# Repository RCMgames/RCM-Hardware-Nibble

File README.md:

# RCM-Hardware-Nibble
v1.8

Half a [BYTE](https://github.com/RCMgames/RCM-Hardware-BYTE)

* 1.08 by 1.12 inches, 27.432 by 28.448 millimeters
* 4 motors
* 4 servos
* 2 additional GPIO pins
* built-in [IMU](https://github.com/RCMgames/useful-code/blob/main/sensors/IMUs/ICM20948/ICM20948_helper.h)
* battery monitoring
* I2C connector on QT PY
* runs on 3-11 volts

program with [RCMv2](https://github.com/RCMgames/RCMv2)

### Tested with the following types of ESP32 QT Py:
| Type of QT Py | PlatformIO name | link to Adafruit |
| ------ | -------- | -------- |
| S3 with 2MB PSRAM |  adafruit_qtpy_esp32s3_n4r2   |  https://www.adafruit.com/product/5700   |
| S3 with 8Mb Flash |  adafruit_qtpy_esp32s3_nopsram   |  https://www.adafruit.com/product/5426   |
| S2 |  adafruit_qtpy_esp32s2   |  https://www.adafruit.com/product/5325  |

Look here for how to program it: https://github.com/RCMgames/RCMv2

Look here for more information and examples of robots: https://github.com/rcmgames

Want slightly larger and 8 motors and 8 servos? Look at the [BYTE](https://github.com/rcmgames/RCM-Hardware-BYTE)

## Options for purchasing

* [PCBWay link](https://www.pcbway.com/project/shareproject/RCMhardwareNibble_v1_8_dbf51cb4.html) (PCBWay will give me a commission without increasing the price for you). (approximately $110 for 2 boards and manufacturing took a month).
* send the gerbers, bill of materials, and ComponentPlacement files (in /PCBproduction-RCM-Nibble) to a PCB manufacturer of your choice (details you may be asked for: min hole 0.25mm, min track/spacing 5/5mil, thickness 1.0mm, 1 oz Cu outer 1.5 oz Cu inner, tell them to not solder the icm20948's exposed pad)

## Components
Solder by hand to complete the assembly of your boards.
| part | links | quantity | notes |
| ----- | ----- | ----- | ----- |
| RCM Nibble circuit board | [options for purchasing](https://github.com/RCMgames/RCM-Hardware-Nibble/tree/main#options-for-purchasing) | 1 | |
| ESP32 QT Py | [compatible QT Py](https://github.com/RCMgames/RCM-Hardware-Nibble/tree/main#tested-with-the-following-types-of-esp32-qt-py) | 1 | |
| 2x4 female header pins | [this](https://www.digikey.com/en/products/detail/sullins-connector-solutions/PPPC042LFBN-RC/810244) or 2 strips of 4 | 1 | for motors |
| 7 female header pins | | 2 | for QT Py |
| 3 male header pins | | 4 | for servos |
| 2 male header pins | | 2 | for extra GPIO pins |
| battery wires | JST RCY OR 9V battery snap | 1 | [Amazon JST RCY](https://www.amazon.com/dp/B00Z04QFN2/) |
| servo buck boost 5v 2A | [Pololu](https://www.pololu.com/product/4085) | 0 or 1 | if you want to supply voltages above or below what servos can accept (supplies other than 5AAs) |

## Acknowledgements
* I would like to thank [PCBWay](https://www.pcbway.com/) for sponsoring prototyping runs of this project. PCBWay produces very nice boards, supports open source hardware, and gave me great support as I worked on this project. Special thanks to Liam!

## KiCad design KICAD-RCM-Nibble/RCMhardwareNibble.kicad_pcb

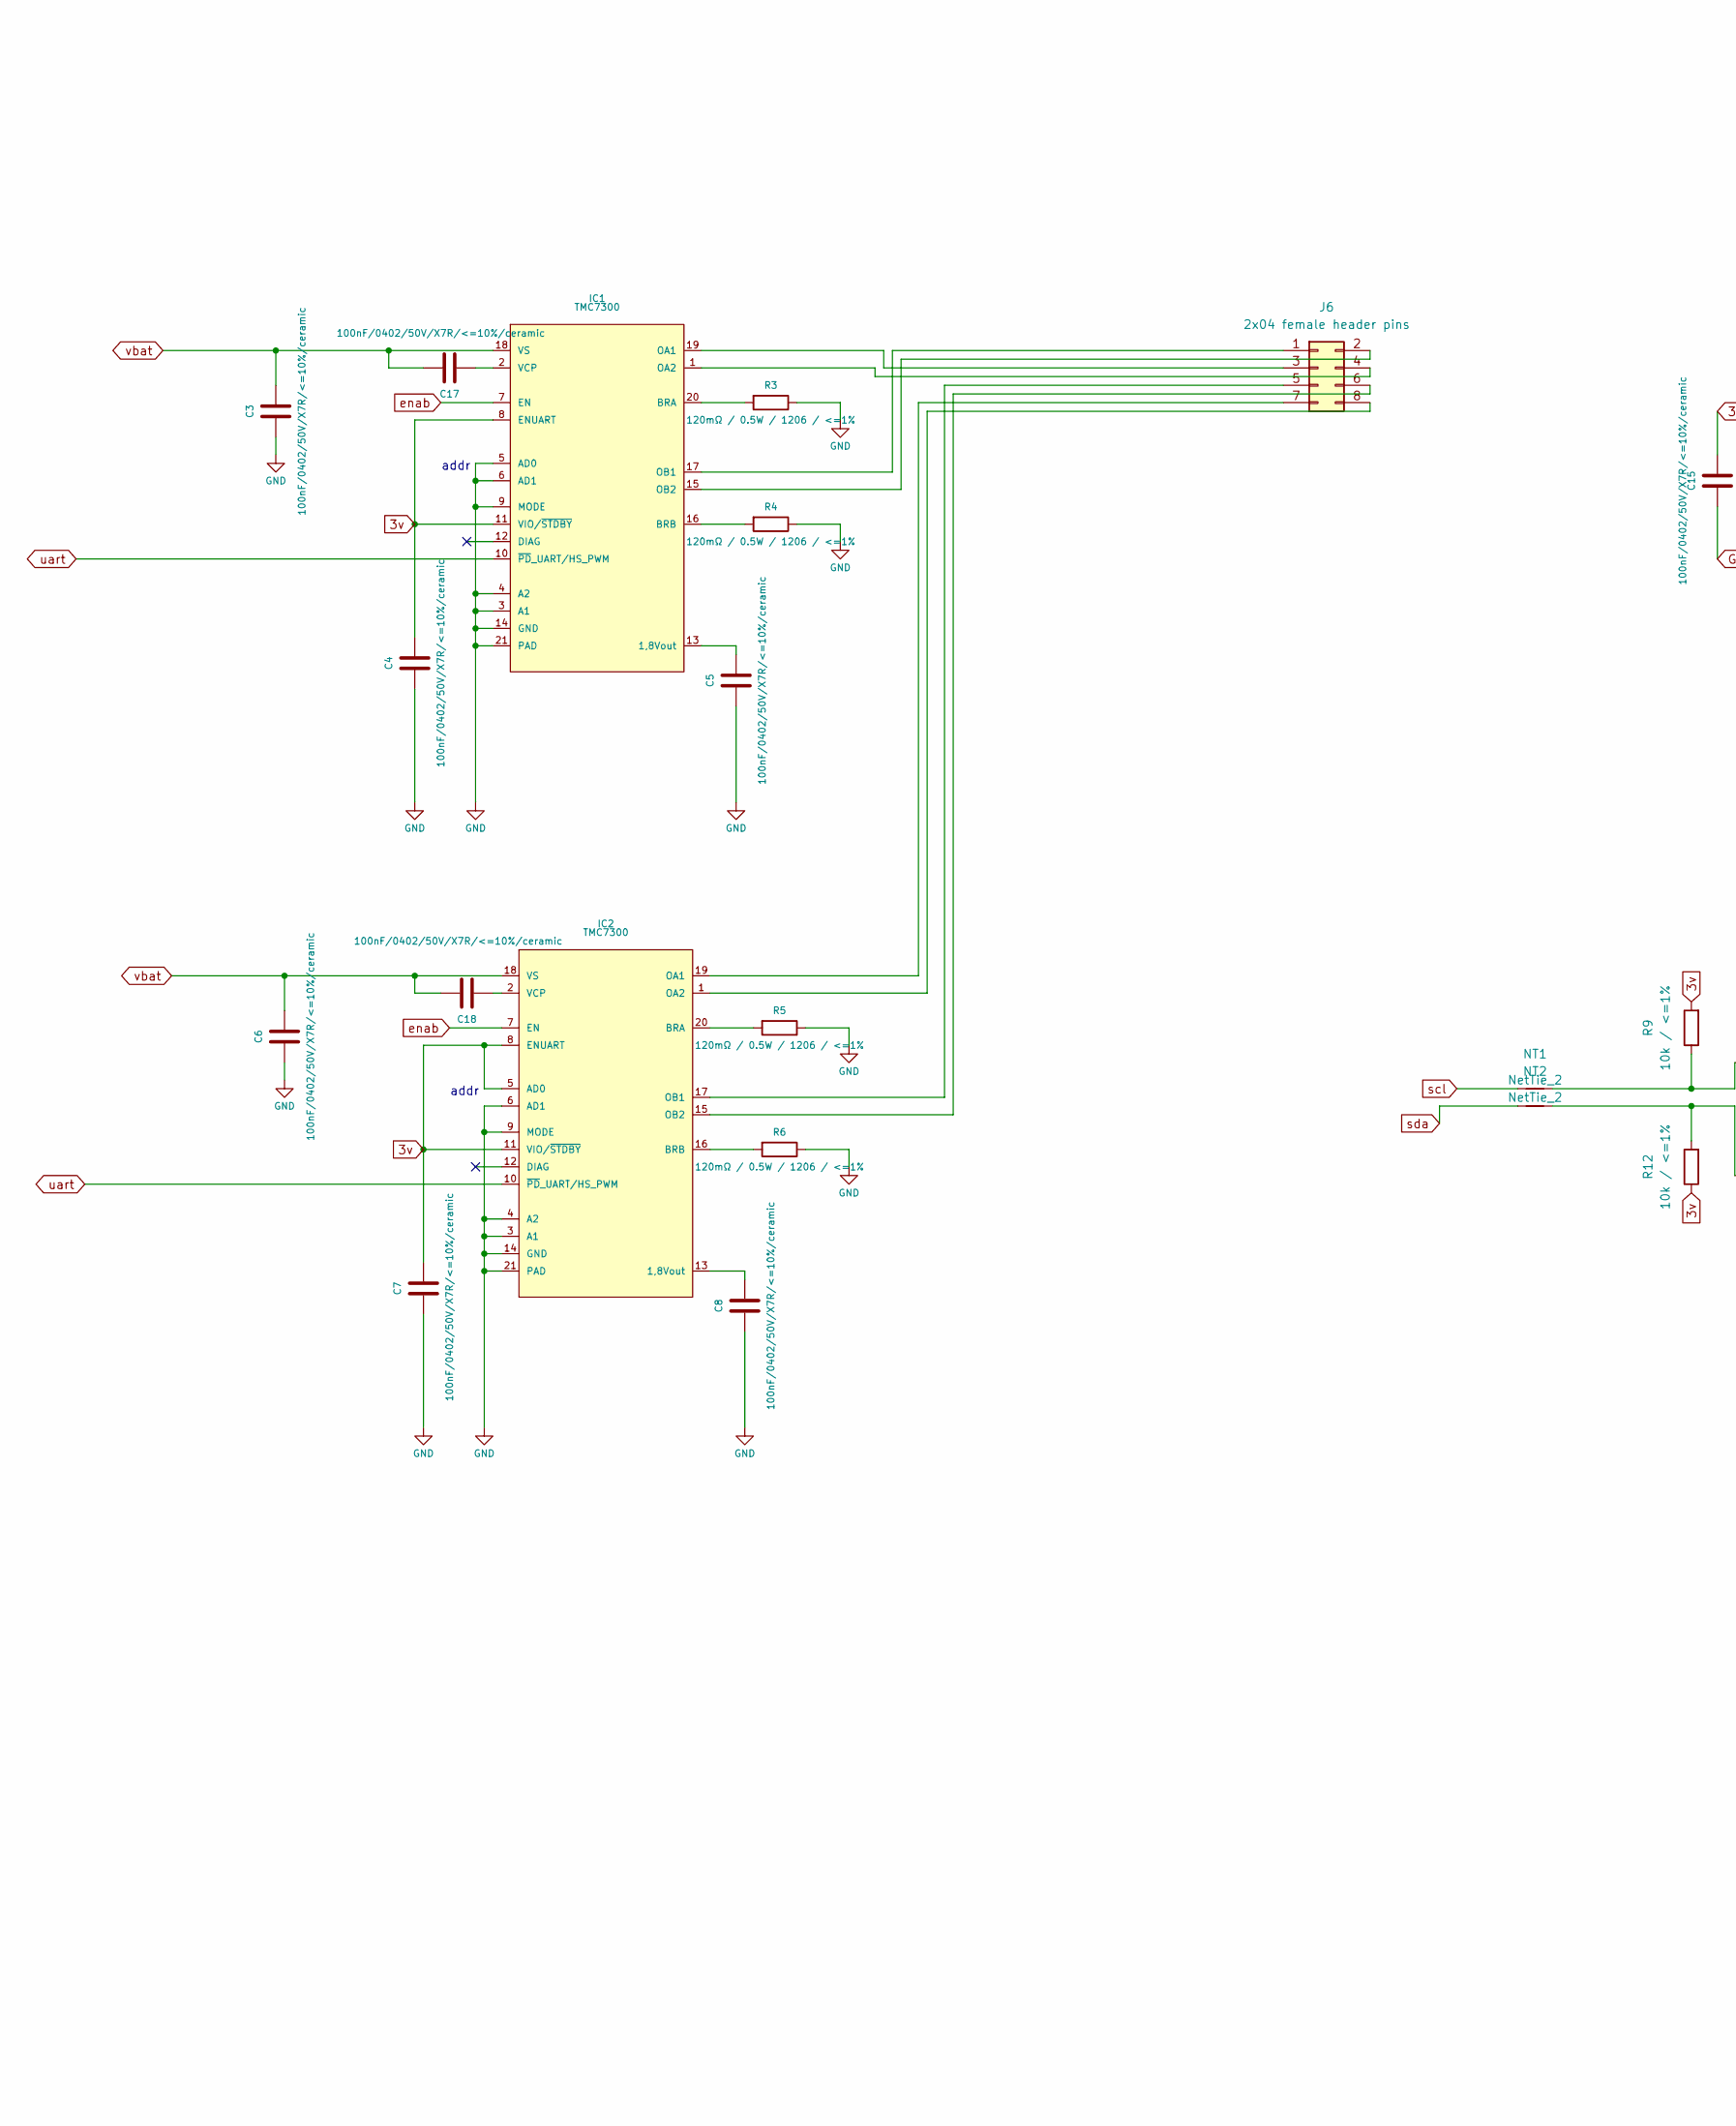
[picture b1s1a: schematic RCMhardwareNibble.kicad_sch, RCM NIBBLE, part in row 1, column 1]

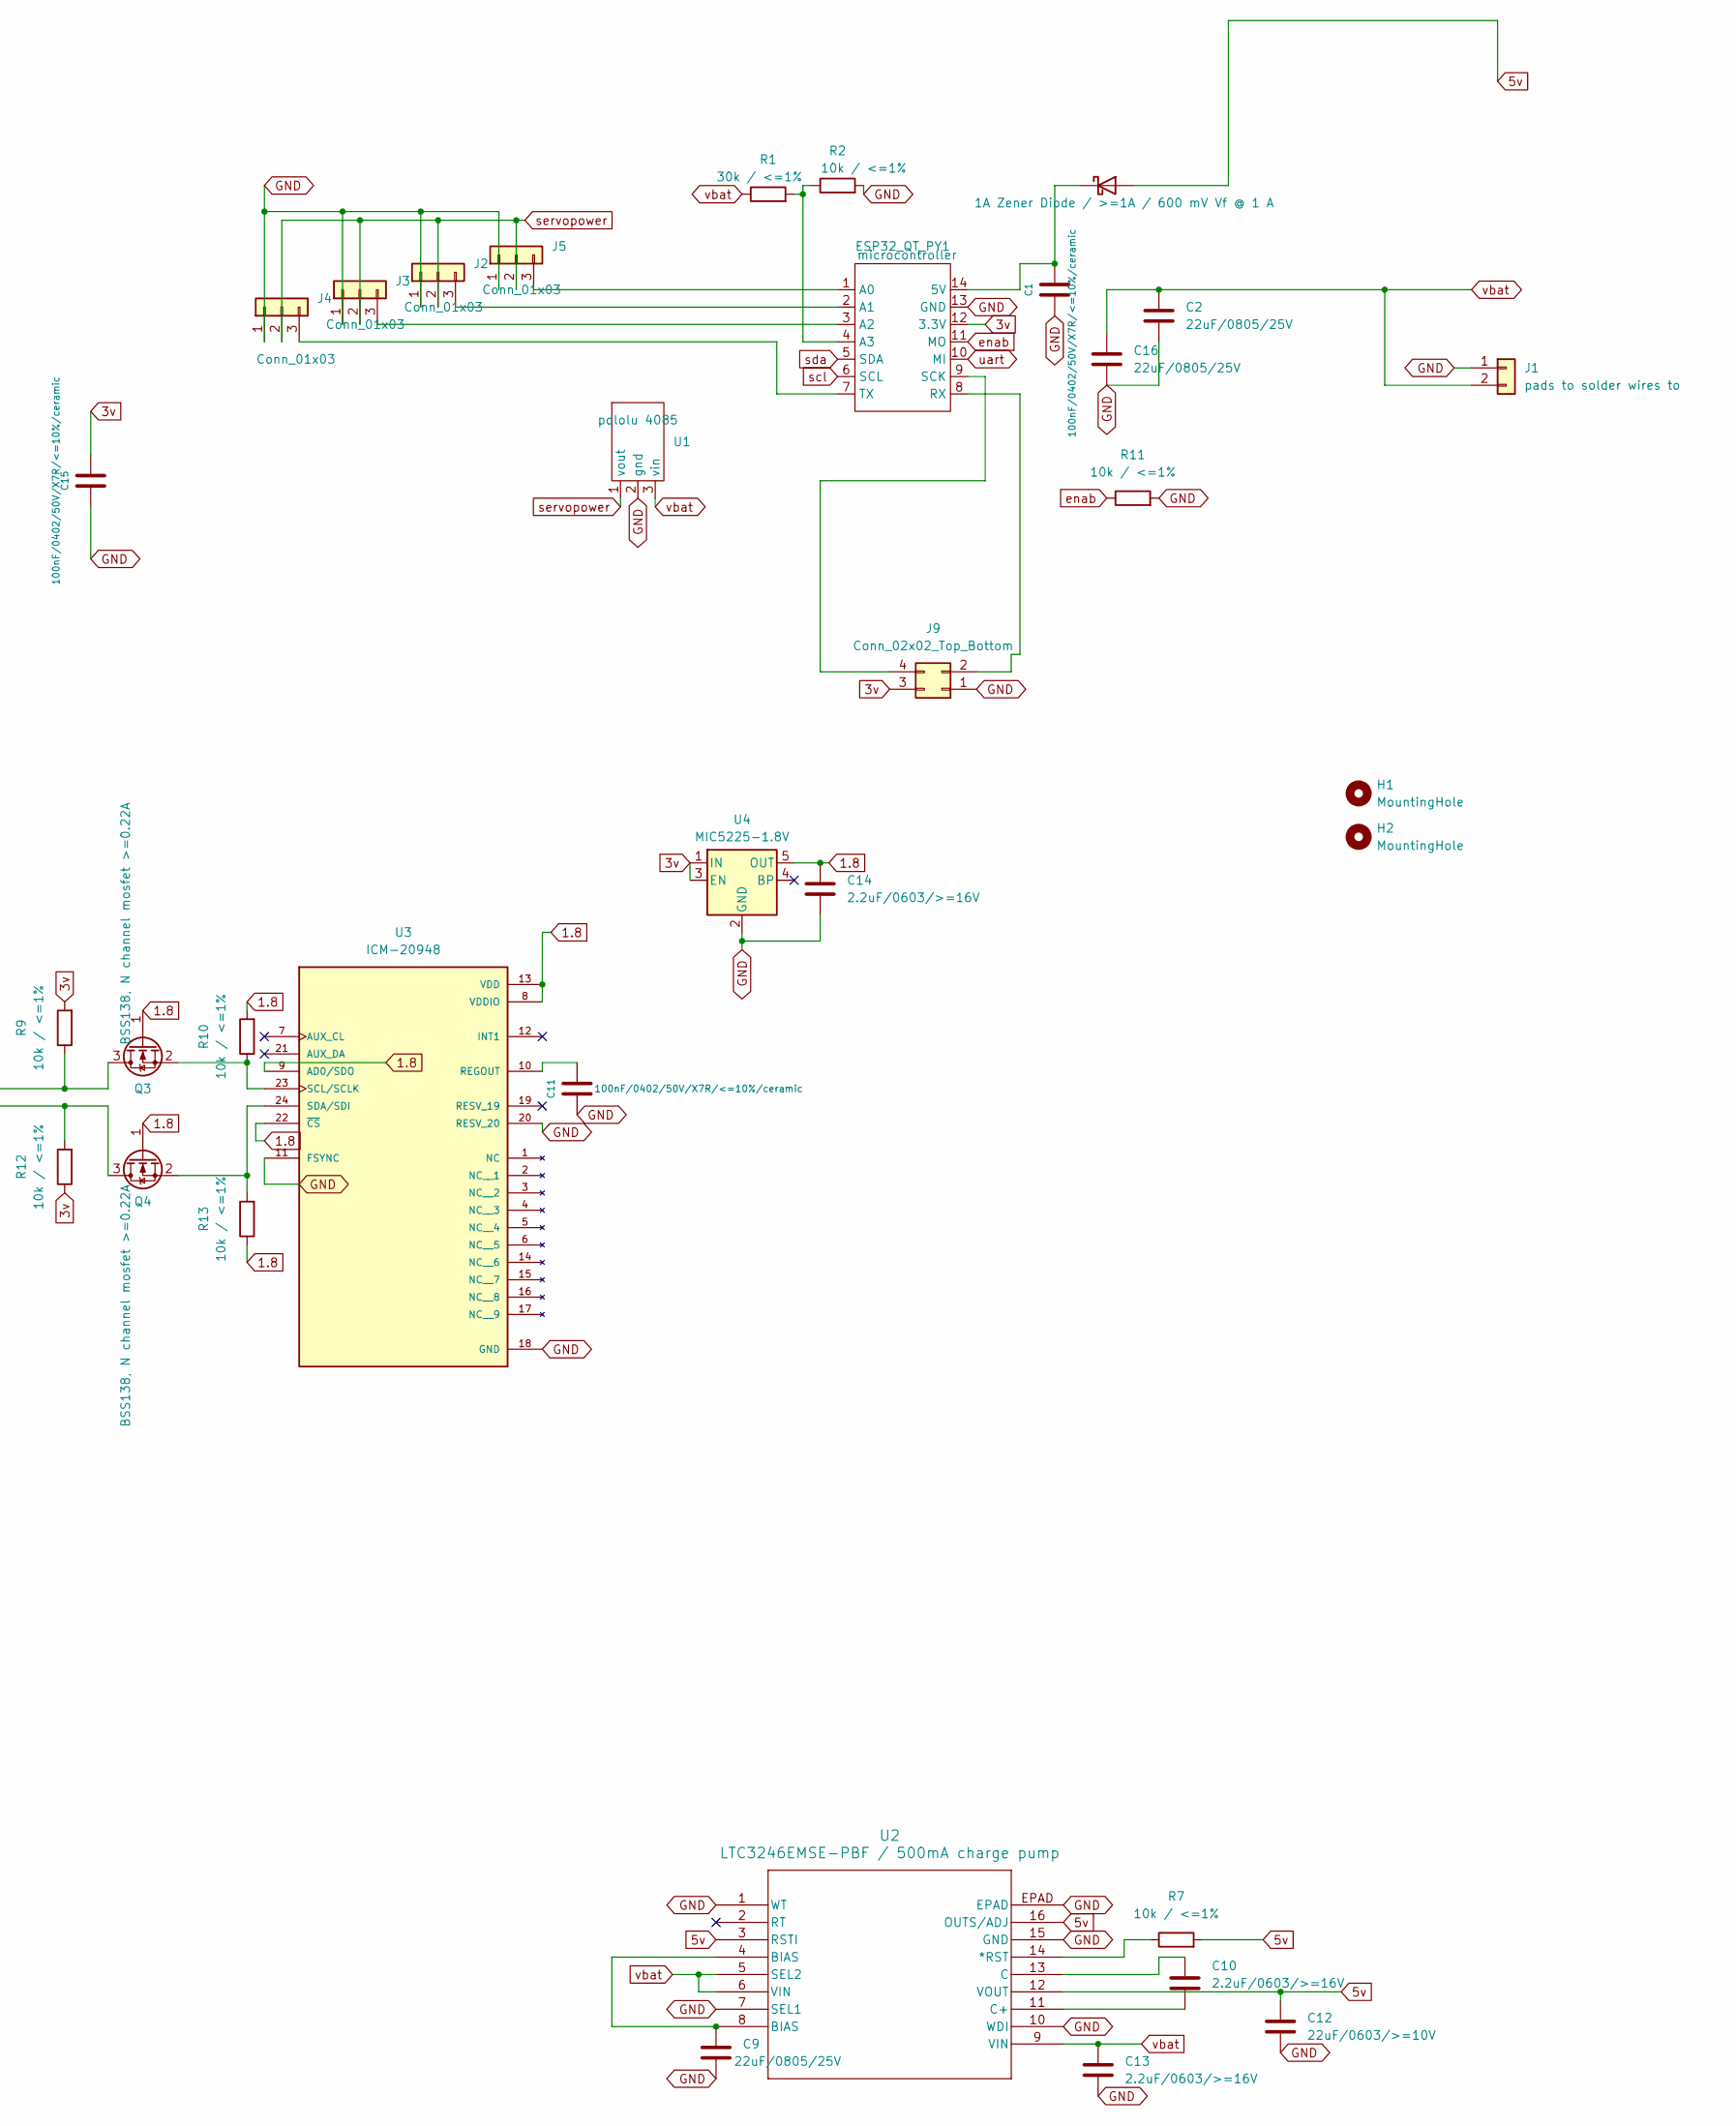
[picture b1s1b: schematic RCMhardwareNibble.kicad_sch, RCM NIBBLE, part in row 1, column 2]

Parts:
C1, C3, C4, C5, C6, C7, C8, C11, C15, C17, C18: 100nF/0402/50V/X7R/<=10%/ceramic; C_0402_1005Metric; mpn GMC04X7R104K50NT; digikey part # 4713-GMC04X7R104K50NTCT-ND
C2, C9, C16: 22uF/0805/25V; C_0805_2012Metric; mpn GMC21X5R226M25NT; digikey part # 4713-GMC21X5R226M25NTCT-ND
C10, C13, C14: 2.2uF/0603/>=16V; C_0603_1608Metric; mpn GMC10X7R225K16NT; digikey part # 4713-GMC10X7R225K16NTCT-ND
C12: 22uF/0603/>=10V; C_0603_1608Metric; mpn GMC10X5R226M10NT; digikey part # 4713-GMC10X5R226M10NTCT-ND
D1: 1A Zener Diode / >=1A / 600 mV Vf @ 1 A; D_SOD-323; mpn GDB5818WS; digikey part # 4786-GDB5818WSCT-ND
ESP32_QT_PY1: microcontroller; ESP32 QT PY; mpn do not place or purchase for PCB assemb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; digikey part # 1528-5426-ND or 1528-5700-ND
H1, H2: MountingHole; MountingHole_2.2mm_M2; mpn DNP; digikey part # n/a
IC1, IC2: TMC7300; QFN-20-1EP_3x3mm_P0.4mm_EP1.65x1.65mm; mpn TMC7300-LA-T; digikey part # 175-TMC7300-LA-TCT-ND
J1: pads to solder wires to; battery wires; mpn do not place or purchase for PCB assemb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
J2, J3, J4, J5: Conn_01x03; PinHeader_1x03_P2.54mm_Vertical; mpn do not place or purchase for PCB assemb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
J6: 2x04 female header pins; PinSocket_2x04_P2.54mm_Vertical; mpn do not place or purchase for PCB assemb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; digikey part # S7107-ND
J9: Conn_02x02_Top_Bottom; PinHeader_2x02_P2.54mm_Vertical; mpn do not place or purchase for PCB assemb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
NT1, NT2: NetTie_2; SolderJumper-2_P1.3mm_Bridged_Pad1.0x1.5mm; mpn do not place or purchase for PCB assemb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; digikey part # n/a
Q3, Q4: BSS138, N channel mosfet >=0.22A; SOT-23; mpn BSS138; digikey part # BSS138CT-ND
R1: 30k / <=1%; R_0402_1005Metric; mpn CR0402-FX-3002GLF; digikey part # CR0402-FX-3002GLFCT-ND
R2, R7, R9, R10, R11, R12, R13: 10k / <=1%; R_0402_1005Metric; mpn CR0402-FX-1002GLF; digikey part # CR0402-FX-1002GLFCT-ND
R3, R4, R5, R6: 120mΩ / 0.5W / 1206 / <=1%; R_1206_3216Metric; mpn CRL1206-FW-R120ELF; digikey part # CRL1206-FW-R120ELFCT-ND
U1: pololu 4085; mpn do not place or purchase for PCB assemb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; digikey part # 2183-4085-ND
U2: LTC3246EMSE-PBF / 500mA charge pump; MSE_16_ADI; mpn LTC3246EMSE#PBF; digikey part # LTC3246EMSE#PBF-ND
U3: ICM-20948; QFN40P300X300X105-24N; mpn ICM-20948; digikey part # 1428-1123-1-ND
U4: MIC5225-1.8V; SOT-23-5; mpn MIC5225-1.8YM5-TR; digikey part # 576-3017-1-ND

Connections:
1.8: C14.1, Q3.1 (G), Q4.1 (G), R10.2, R13.1, U3.8 (VDDIO), U3.9 (AD0/SDO), U3.13 (VDD), U3.22 (~CS), U4.5 (OUT)
3v: C4.1, C7.1, C15.1, ESP32_QT_PY1.12 (3.3V), IC1.8 (ENUART), IC1.11 (VIO/~STDBY), IC2.5 (AD0), IC2.8 (ENUART), IC2.11 (VIO/~STDBY), J9.3, R9.2, R12.1, U4.1 (IN), U4.3 (EN)
5v: C12.2, D1.2 (A), R7.2, U2.3 (RSTI), U2.12 (VOUT), U2.16 (OUTS/ADJ)
GND: C1.2, C2.2, C3.2, C4.2, C5.2, C6.2, C7.2, C8.2, C9.1, C11.2, C12.1, C13.2, C14.2, C15.2, C16.2, ESP32_QT_PY1.13 (GND), IC1.3 (A1), IC1.4 (A2), IC1.5 (AD0), IC1.6 (AD1), IC1.9 (MODE), IC1.14 (GND), IC1.21 (PAD), IC2.3 (A1), IC2.4 (A2), IC2.6 (AD1), IC2.9 (MODE), IC2.14 (GND), IC2.21 (PAD), J1.1, J2.1, J3.1, J4.1, J5.1, J9.1, R2.2, R3.1, R4.1, R5.1, R6.1, R11.2, U1.2 (gnd), U2.1 (WT), U2.7 (SEL1), U2.10 (WDI), U2.15 (GND), U2.EPAD, U3.11 (FSYNC), U3.18 (GND), U3.20 (RESV_20), U4.2 (GND)
unnamed: C9.2, U2.4 (BIAS), U2.8 (BIAS)
unnamed: C1.1, D1.1 (K), ESP32_QT_PY1.14 (5V)
unnamed: ESP32_QT_PY1.1 (A0), J5.3
unnamed: ESP32_QT_PY1.2 (A1), J2.3
unnamed: ESP32_QT_PY1.3 (A2), J3.3
unnamed: ESP32_QT_PY1.4 (A3), R1.2, R2.1
unnamed: ESP32_QT_PY1.8 (RX), J9.2
unnamed: ESP32_QT_PY1.9 (SCK), J9.4
unnamed: ESP32_QT_PY1.7 (TX), J4.3
unnamed: C5.1, IC1.13 (1,8Vout)
unnamed: IC1.20 (BRA), R3.2
unnamed: IC1.16 (BRB), R4.2
unnamed: IC1.19 (OA1), J6.3
unnamed: IC1.1 (OA2), J6.4
unnamed: IC1.17 (OB1), J6.1
unnamed: IC1.15 (OB2), J6.2
unnamed: C17.2, IC1.2 (VCP)
unnamed: C8.1, IC2.13 (1,8Vout)
unnamed: IC2.20 (BRA), R5.2
unnamed: IC2.16 (BRB), R6.2
unnamed: IC2.19 (OA1), J6.7
unnamed: IC2.1 (OA2), J6.8
unnamed: IC2.17 (OB1), J6.5
unnamed: IC2.15 (OB2), J6.6
unnamed: C18.2, IC2.2 (VCP)
unnamed: NT1.2, Q3.3 (D), R9.1
unnamed: Q3.2 (S), R10.1, U3.23 (SCL/SCLK)
unnamed: NT2.2, Q4.3 (D), R12.2
unnamed: Q4.2 (S), R13.2, U3.24 (SDA/SDI)
unnamed: R7.1, U2.14 (*RST)
unnamed: C10.1, U2.13 (C)
unnamed: C10.2, U2.11 (C+)
unnamed: C11.1, U3.10 (REGOUT)
enab: ESP32_QT_PY1.11 (MO), IC1.7 (EN), IC2.7 (EN), R11.1
scl: ESP32_QT_PY1.6 (SCL), NT1.1
sda: ESP32_QT_PY1.5 (SDA), NT2.1
servopower: J2.2, J3.2, J4.2, J5.2, U1.1 (vout)
uart: ESP32_QT_PY1.10 (MI), IC1.10 (~PD_UART/HS_PWM), IC2.10 (~PD_UART/HS_PWM)
vbat: C2.1, C3.1, C6.1, C13.1, C16.1, C17.1, C18.1, IC1.18 (VS), IC2.18 (VS), J1.2, R1.1, U1.3 (vin), U2.5 (SEL2), U2.6 (VIN), U2.9 (VIN)

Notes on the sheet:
addr

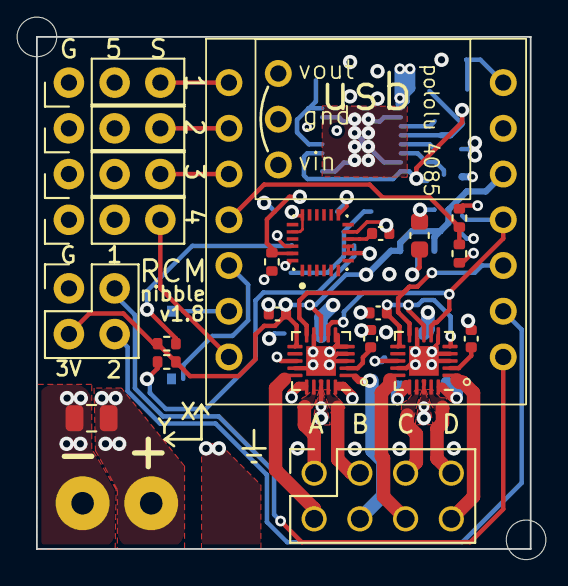
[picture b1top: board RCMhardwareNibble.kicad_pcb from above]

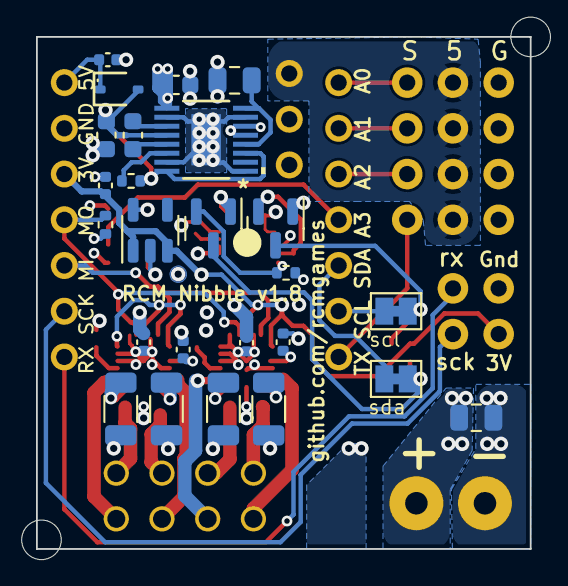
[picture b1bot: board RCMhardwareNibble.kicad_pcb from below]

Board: 4 copper layers, 27.4 x 28.4 mm, 51 parts (25 on the bottom side), 43 nets.

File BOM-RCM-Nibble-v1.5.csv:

"Reference","Value","Footprint","Datasheet","Manufacturer","Package","digikey part #","link","mount_type","mpn","Qty"
"C1, C3-C8, C11, C15, C17, C18","100nF/0402/16V/X7R/<=10%/ceramic","Capacitor_SMD:C_0402_1005Metric","~","any","0402","4713-GMC04X7R104K50NTCT-ND","https://www.digikey.cn/en/products/detail/cal-chip-electroni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","smt","GMC04X7R104K50NT","11"
"C2, C9, C16","22uF/0805/>=16V","Capacitor_SMD:C_0805_2012Metric","~","any","0805","4713-GMC21X5R226M25NTCT-ND","https://www.digikey.cn/en/products/detail/cal-chip-electroni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","smt","GMC21X5R226M25NT","3"
"C10, C13, C14","2.2uF/0603/>=16V","Capacitor_SMD:C_0603_1608Metric","~","any","0603","4713-GMC10X7R225K16NTCT-ND","https://www.digikey.cn/en/products/detail/cal-chip-electroni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","smt","GMC10X7R225K16NT","3"
"C12","22uF/0603/>=10V","Capacitor_SMD:C_0603_1608Metric","~","any","0603","4713-GMC10X5R226M10NTCT-ND","https://www.digikey.cn/en/products/detail/cal-chip-electroni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","smt","GMC10X5R226M10NT","1"
"D1","1A Zener Diode  / >=1A / 600 mV Vf @ 1 A","Diode_SMD:D_SOD-323","~","Good-Ark Semiconductor","D_SOD-323","4786-GDB5818WSCT-ND","https://www.digikey.com/en/products/detail/good-ark-semicond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","smt","GDB5818WS","1"
"ESP32_QT_PY1","microcontroller","!RCMhardware footprints:ESP32 QT PY","~","do not place or purchase for PCB assembly","tht","1528-5426-ND or 1528-5700-ND","","tht","do not place or purchase for PCB assembly","1"
"H1, H2","MountingHole","MountingHole:MountingHole_2.2mm_M2","~","n/a","n/a","n/a","n/a","n/a","n/a","2"
"IC1, IC2","TMC7300","!RCMhardware footprints:QFN-20-1EP_3x3mm_P0.4mm_EP1.65x1.65mm","https://www.analog.com/media/en/technical-documentation/data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","Analog Devices","QFN-20-1EP_3x3mm_P0.4mm_EP1.65x1.65mm","175-TMC7300-LA-TCT-ND","https://www.digikey.com/en/products/detail/analog-devices-in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","smt","TMC7300-LA-T","2"
"J1","pads to solder wires to","!RCMhardware footprints:battery wires","JST RCY suggested","~","tht","~","https://www.amazon.com/dp/B00Z04QFN2/","tht","do not place or purchase for PCB assembly","1"
"J2-J5","Conn_01x03","Connector_PinHeader_2.54mm:PinHeader_1x03_P2.54mm_Vertical","~","~","tht","~","~","tht","do not place or purchase for PCB assembly","4"
"J6","2x04 female header pins","!RCMhardware footprints:PinSocket_2x04_P2.54mm_Vertical","~","do not place or purchase for PCB assembly","tht","S7107-ND","https://www.digikey.com/en/products/detail/sullins-connector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","tht","do not place or purchase for PCB assembly","1"
"J9","Conn_02x02_Top_Bottom","Connector_PinHeader_2.54mm:PinHeader_2x02_P2.54mm_Vertical","~","do not place or purchase for PCB assembly","tht","~","~","tht","do not place or purchase for PCB assembly","1"
"NT1, NT2","NetTie_2","Jumper:SolderJumper-2_P1.3mm_Bridged_Pad1.0x1.5mm","~","n/a","n/a","n/a","n/a","tht","do not place or purchase for PCB assembly","2"
"Q3, Q4","BSS138, N channel mosfet >=0.22A","Package_TO_SOT_SMD:SOT-23","https://www.onsemi.com/pub/Collateral/BSS138-D.PDF","onsemi","SOT-23","BSS138CT-ND","https://www.digikey.com/en/products/detail/onsemi/BSS138/244210","smt","BSS138","2"
"R1","30k / <=1%","Resistor_SMD:R_0402_1005Metric","~","any","0402","CR0402-FX-3002GLFCT-ND","https://www.digikey.com/en/products/detail/bourns-inc/CR0402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","smt","CR0402-FX-3002GLF","1"
"R2, R7, R9-R13","10k / <=1%","Resistor_SMD:R_0402_1005Metric","~","any","0402","CR0402-FX-1002GLFCT-ND","https://www.digikey.com/en/products/detail/bourns-inc/CR0402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","smt","CR0402-FX-1002GLF","7"
"R3-R6","120mΩ / 0.5W / 1206 / <=1%","Resistor_SMD:R_1206_3216Metric","~","any","1206","CRL1206-FW-R120ELFCT-ND","https://www.digikey.com/en/products/detail/bourns-inc/CRL120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","smt","CRL1206-FW-R120ELF","4"
"U1","pololu 4085","!RCMhardware footprints:pololu 4085","~","Pololu","tht","2183-4085-ND","https://www.digikey.com/en/products/detail/pololu-corporatio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","tht","do not place or purchase for PCB assembly","1"
"U2","LTC3246EMSE-PBF / 500mA charge pump","!RCMhardware footprints:MSE_16_ADI","LTC3246EMSE-PBF","Analog Devices","16-TFSOP (0.118"", 3.00mm Width) Exposed Pad","LTC3246EMSE#PBF-ND","https://www.digikey.com/en/products/detail/analog-devices-in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","smt","LTC3246EMSE#PBF","1"
"U3","ICM-20948","!RCMhardware footprints:QFN40P300X300X105-24N","https://invensense.tdk.com/wp-content/uploads/2016/06/DS-000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","TDK InvenSense","24-QFN (3x3)","1428-1123-1-ND","https://www.digikey.com/en/products/detail/tdk-invensense/IC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","smt","ICM-20948","1"
"U4","MIC5225-1.8V","Package_TO_SOT_SMD:SOT-23-5","https://ww1.microchip.com/downloads/en/DeviceDoc/mic5225.pdf","Microchip","SC-74A, SOT-753","576-3017-1-ND","https://www.digikey.com/en/products/detail/microchip-technol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","smt","MIC5225-1.8YM5-TR","1"

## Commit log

2024-03-28 v1.4.0
2024-04-03 add pictures
2024-04-16 v1.5.0
2024-04-16 close #3 close #4
2024-05-04 v1.6
2024-05-05 v1.6.1
2024-05-05 update photos
2024-05-07 working on v1.7
2024-05-08 v1.7
2024-05-09 v1.7.0
2024-05-10 v1.7.1
2024-05-15 update production files
2024-05-16 v1.8
2024-06-02 add renders v1.8
2024-06-07 photos
2026-05-10 export step file
